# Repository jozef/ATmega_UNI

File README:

NAME

    ATmega UNI - Universal ATmega PCB in Arduino UNO (shield) size

DESCRIPTION

    ATmega PCB designed in KiCad with an aim to be as universali used as
    possible in a shape and dimensions of Arduino UNO.

LICENSE

    This is free software, licensed under the MIT License.

AUTHOR

        Jozef Kutej

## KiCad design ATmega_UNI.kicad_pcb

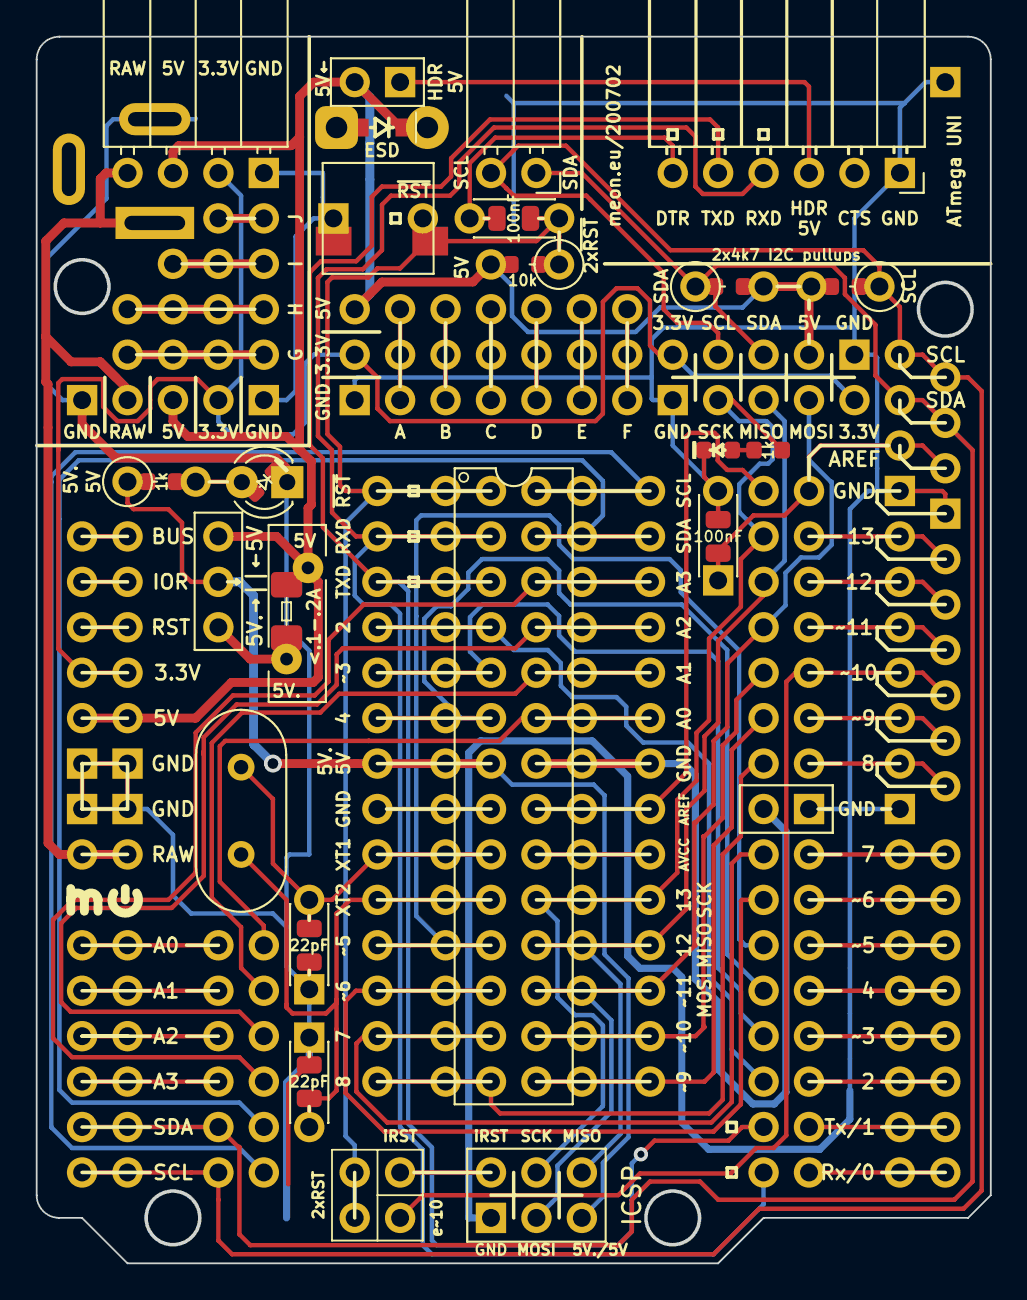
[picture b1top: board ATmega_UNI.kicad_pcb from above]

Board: 2 copper layers, 53.2 x 68.5 mm, 61 parts (0 on the bottom side), 69 nets.

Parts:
C11, C12: 22pF; C_0805_2012Metric_no_lines
C13, C14: 22pF; C_Disc_D4.3mm_W1.9mm_P5.00mm_doubleside
C21, C31: 100nF; C_0805_2012Metric_no_lines
C22, C32: 100nF; C_Disc_D4.3mm_W1.9mm_P5.00mm_doubleside
D9, D12: PWR; LED_0603_1608Metric_symbol
D81: ESD prot.; D_SOD-323_HandSoldering_F_SilkS_Sym
D82: ESD prot.; D_DO-15_P5.08mm_Vertical_KathodeUp_no_lines
D92: PWR; LED_D3.0mm_doubleside
F1: MF-R010 <200mA; Fuse_Bourns_MF-R010
F2: 1206 PPTC <200mA; Fuse_1206_3216Metric_Pad1.42x1.75mm_HandSolder_no_lines
J1, J11: PDIP_1_to_14; PinSocket_1x14_P2.54mm_Vertical_no_lines
J2, J22: PDIP_15_to_28; PinSocket_1x14_P2.54mm_Vertical_no_lines
J7: USB_to_TTL; PinSocket_1x06_P2.54mm_Horizontal_doublesided
J8: ICSP; PinHeader_2x03_P2.54mm_Vertical_closed
J62, J63, J64: 4uni; PinHeader_1x07_P2.54mm_Vertical_no_lines
J65, J66: 4uni; PinHeader_1x04_P2.54mm_Vertical_no_lines
J67: 4uni; PinHeader_1x03_P2.54mm_Vertical_no_lines
J68: 2uni; PinHeader_1x02_P2.54mm_Vertical_no_lines
J79: GND; PinHeader_1x01_P2.54mm_Vertical_no_lines
J81: ICSP; PinHeader_2x02_P2.54mm_Vertical_no_lines
J92: D8-D13; PinHeader_1x07_P2.54mm_Vertical_no_lines
J93: D0-D7; PinHeader_1x08_P2.54mm_Vertical_no_lines
J94: A0-A3; PinHeader_1x06_P2.54mm_Vertical_no_lines
J95: Power; PinSocket_1x04_P2.54mm_Horizontal_doublesided
J96: Power; PinHeader_1x04_P2.54mm_Vertical_no_lines
J97: Barrel_Jack_Switch; BarrelJack_Wuerth_6941xx301002_no_lines
J98, J100: extra_gnd; PinHeader_1x01_P2.54mm_Vertical_no_lines
J611, J612: I2C; PinSocket_1x05_P2.54mm_Vertical_no_lines
J613: I2C; PinSocket_1x02_P2.54mm_Horizontal_doubleside
JP9: HDR→5V; PinHeader_1x02_P2.54mm_Vertical_closed
JP10: no_A_limit; PinHeader_1x03_P2.54mm_Vertical_closed
JP11: A-GND; PinHeader_1x02_P2.54mm_Vertical_closed
Je92: eD8-eD13; PinHeader_1x07_P2.54mm_Vertical_no_lines
Je93: eD0-eD7; PinHeader_1x08_P2.54mm_Vertical_no_lines
Je94: eA0-eA3; PinHeader_1x06_P2.54mm_Vertical_no_lines
R1: 4k7; R_0603_1608Metric_no_lines
R2: 10k; R_0603_1608Metric_no_lines
R3: 4k7 pullups; R_0603_1608Metric_no_lines
R9, R11: 1k; R_0603_1608Metric_no_lines
R12, R32: 4k7 THT; R_Axial_DIN0207_L6.3mm_D2.5mm_P3.81mm_Vertical_doubleside
R22: 10k THT; R_Axial_DIN0207_L6.3mm_D2.5mm_P3.81mm_Vertical_doubleside
R92: 1k; R_Axial_DIN0207_L6.3mm_D2.5mm_P3.81mm_Vertical_doubleside
SW1: Reset; SW_PUSH_6.2mm_DTST_6
SW2: Reset; SW_SPST_EVQPE1_no_lines
U1: ATmega328P-PU; DIP-28_W7.62mm_big_holes
U9: Arduino_Uno_Black; Arduino_Uno_Black_2rows
Y1: 16MHz; Crystal_HC49-U_Vertical

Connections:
+3V3: J62.1, J95.2, J96.2, J611.5, J612.5, U9.94
+5V: D81.1, D82.1, F1.2, F2.2, J64.1, J95.3, J96.3, J612.2, JP9.2, JP10.3, R1.2, R2.1, R3.2, R12.2, R22.2, R32.2, U9.6
+5V_jmp: J1.7, J8.2, J11.7, JP10.2, R9.2, R92.1, U1.7
+5V_lim: F1.1, F2.1, JP10.1
DTR: C21.2, C22.1, J7.6
GND: C11.2, C12.2, C13.2, C14.2, C31.1, C32.1, D9.1, D12.1, D81.2, D82.2, D92.1, J7.1, J8.6, J63.1, J79.1, J95.1, J96.1, J97.2, J98.1, J100.1, J611.1, J612.1, JP11.1, SW1.2, SW2.2, U9.3, U9.5, U9.21
MISO: J2.4, J8.1, J22.4, J92.5, J611.3, U1.18
MOSI: J2.3, J8.4, J22.3, J92.4, J611.4, U1.17
unnamed: C31.2, C32.2, Je92.7, U9.20
unnamed: D9.2, D92.2, R9.1, R92.2
unnamed: D12.2, R11.2
unnamed: J62.2, J63.2, J64.2
unnamed: J62.3, J63.3, J64.3
unnamed: J62.4, J63.4, J64.4
unnamed: J62.5, J63.5, J64.5
unnamed: J62.6, J63.6, J64.6
unnamed: J62.7, J63.7, J64.7
unnamed: J65.1, J66.1, J67.1, J68.1
unnamed: J65.2, J66.2, J67.2, J68.2
unnamed: J65.3, J66.3, J67.3
unnamed: J65.4, J66.4
unnamed: Je92.1, U9.12
unnamed: Je92.2, U9.13
unnamed: Je92.4, U9.15
unnamed: Je92.5, U9.16
unnamed: Je92.6, U9.17
unnamed: Je93.1, U9.30
unnamed: Je93.2, U9.31
unnamed: Je93.3, U9.32
unnamed: Je93.4, U9.1
unnamed: Je93.5, U9.2
unnamed: Je93.6, U9.9
unnamed: Je93.7, U9.10
unnamed: Je93.8, U9.11
unnamed: Je94.1, U9.23
unnamed: Je94.2, U9.24
unnamed: Je94.3, U9.25
unnamed: Je94.4, U9.26
PDIP4: J1.4, J11.4, J93.3, U1.4
PDIP5: J1.5, J11.5, J93.4, U1.5
PDIP6: J1.6, J11.6, J93.5, U1.6
PDIP11: J1.11, J11.11, J93.6, U1.11
PDIP12: J1.12, J11.12, J93.7, U1.12
PDIP13: J1.13, J11.13, J93.8, U1.13
PDIP14: J1.14, J11.14, J92.1, U1.14
PDIP15: J2.1, J22.1, J92.2, U1.15
PDIP16: J2.2, J22.2, J92.3, U1.16
PDIP20: J2.6, J22.6, U1.20
PDIP21: J2.7, J22.7, J92.7, U1.21
PDIP23: J2.9, J22.9, J94.1, U1.23
PDIP24: J2.10, J22.10, J94.2, U1.24
PDIP25: J2.11, J22.11, J94.3, U1.25
PDIP26: J2.12, J22.12, J94.4, U1.26
PDIP27: J2.13, J22.13, J94.5, U1.27
PDIP28: J2.14, J22.14, J94.6, U1.28
RAW: J95.4, J96.4, J97.1, U9.99
RXD: J1.2, J7.4, J11.2, J93.1, U1.2
SCK: J2.5, J8.3, J22.5, J92.6, J611.2, R11.1, U1.19
SCL: J612.4, J613.2, Je94.6, R3.1, R32.1, U9.28
SDA: J612.3, J613.1, Je94.5, R1.1, R12.1, U9.27
TXD: J1.3, J7.5, J11.3, J93.2, U1.3
USB_5V: J7.3, JP9.1
X1GND: J1.8, J11.8, U1.8
X2GND: J2.8, J22.8, JP11.2, U1.22
XTAL1: C11.1, C13.1, J1.9, J11.9, U1.9, Y1.2
XTAL2: C12.1, C14.1, J1.10, J11.10, U1.10, Y1.1
~RST: C21.1, C22.2, J1.1, J11.1, J81.1, J81.3, R2.2, R22.1, SW1.1, SW2.1, U1.1
~eRST: J81.4, Je92.3, U9.14
~iRST: J8.5, J81.2

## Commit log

2019-05-04 initial version; proof of concept; a bootloader programmer
2019-05-05 added more pads, i2c pullups, only spi and i2c wired together on pcb
2019-05-05 raw D, usb pwr jumper, pwr led, back side labels
2019-05-06 add universal and i2c connectors, typooo fix
2019-05-06 2 more general pads, mark connected pins
2019-05-06 use SOD-323 Schottky diode for reverse protection
2019-05-07 add pwd switch, reset button, update labels
2019-05-08 add capacitors for 3.3V
2019-05-29 add resistors also to the kathode of rgb leds, update labels and highlight connected pads
2019-05-30 change pins shapes, labels
2019-08-03 rm cp2102, normal tht instead of rgb led pads
2019-08-03 add icsp header
2019-08-04 rst jumper, spi pins via jumpers, more lables
2019-08-04 jumper instead of switch
2019-08-05 smaller pitch for the radia condensators
2019-08-07 add more 3.3V pins
2019-09-19 connection jumpers between microcontroller and shield pins
2019-09-21 tht push reset button
2019-09-21 switch female/male connectors, add more SilkS lines
2019-09-22 use smd led for power, move away i2c pull-up resistors and around to make space for zif socket
2019-09-22 add cp2102 mounting pin
2019-09-23 bump-up the version
2019-09-23 rotate sck led, oval holes, connected pins with SilkS symbols, fix power src text on back
2019-09-25 move i2c to have more space for zif socket, wider 5V from raw tracks
2019-09-25 move reset jumper a little further from icsp
2019-09-28 cleaner SilkS look
2019-09-29 add MF-R010 over current protection for microcontroller part, add 3x5 universal THT pins
2019-10-02 use tantalum capacitors for voltage regulator
2019-10-02 tracks clean-up
2019-10-02 mark doblesided parts
2019-10-06 use power shield
2019-10-10 add couple more universal pins
2019-10-20 all smd also as tht
2019-10-20 add i2c top connector, dtr+r-reset also tht
2019-10-21 clean-up
2019-10-21 add jack connector
2019-10-25 tidy-up
2019-10-28 5V(.) and GND via jumpers for U1
2019-10-28 add one more universal pin row
2019-11-02 also smd fuse, tidy-up
2019-11-05 version++
2019-11-27 add sd reset switch
2019-11-27 tidy-up pad shapes
2019-11-27 more b.sliks art
2019-11-27 move pwr led and r
2019-12-08 add one more extra gnd pin
2020-02-09 move smt switch away from 5V pins
2020-02-28 replace one i2c header with spi
2020-03-17 use one less jumper for GND connect
2020-03-25 better visible f/b-silk lines to the 50mills shifted pins
2020-05-23 add aref jumper, capacitor to aref, sck/13 led smd-only
2020-05-25 add one pin for icsp rst jumper neutral position, crystal label update
2020-05-28 sda&scl also via jumpers
2020-05-31 remove jack to 5V jumper
2020-06-03 add esd diode
2020-07-02 allow jumper conn. D10 and icsp rst
